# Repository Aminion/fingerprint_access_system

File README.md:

# Fingerprint Access System

## Project Overview

This project implements a complete biometric access control. It handles asynchronous UART communication for fingerprint authentication, ADC measurements for battery diagnostics, and PWM control for physical actuation. The firmware is written entirely in `no_std` Rust, utilizing the Embassy framework for concurrent, event-driven execution without the overhead of a traditional RTOS.

### Core Capabilities
* **Biometric Authentication:** Secure, asynchronous UART communication with a fingerprint module for user enrollment and verification.
* **PWM-Optimized Actuation:** Implementation of a "peak-and-hold" solenoid drive mechanism using Hardware PWM, significantly reducing active power consumption and thermal load.
* **Ratiometric Battery Diagnostics:** A custom ADC measurement strategy utilizing an external TL431 reference to accurately calculate battery capacity, regardless of internal 3.3V rail voltage sag.
* **Zero-State Power Gating:** Physical isolation of analog subsystems (voltage dividers, reference chips) via GPIO-controlled switching, ensuring 0mA draw from these components during system standby.

## Software Stack & Hardware Architecture

### Software
* **Language:** Rust (`no_std`)
* **Framework:** Embassy (Embedded Async)
* **Concurrency Model:** `embassy-executor` for lightweight task scheduling and interrupt management.

### Hardware & Peripherals
* **Microcontroller:** STM32G031K8 (Nucleo-32)
* **Sensor:** GROW R503
* **Power Supply:** 4xAAA NiMH Battery Pack (~4.0V - 6.0V)
* **Peripheral Utilization:**
  * **PWM (Pulse Width Modulation):** Configured to manage the solenoid's current draw, as well as generate user-feedback tones.
  * **ADC (Analog-to-Digital Converter):** Utilizes extended sample timing (`Cycles160_5`) and floating-point calibration math to bypass hardware limitations.
  * **UART (Universal Asynchronous Receiver-Transmitter):** Handles packet-based serial data transfer with the biometric sensor.
  * **GPIO:** Configured for push-pull power switching and standard digital I/O.

## Engineering Challenges Solved

### 1. Solenoid Power Optimization (Peak-and-Hold)
Solenoids require a high initial "pull-in" current to overcome mechanical inertia, but require significantly less current to maintain the unlocked state. Driving a solenoid at 100% duty cycle for the duration of the unlock period wastes battery capacity and generates excess heat.
* **Solution:** The firmware utilizes hardware PWM to drive the actuating transistor. It applies a 100% duty cycle for the initial actuation phase (e.g., 100ms), then instantly drops the duty cycle to a calculated holding percentage (e.g., 30%). This reduces the holding power consumption by up to 70% while keeping the lock disengaged.

### 2. Ratiometric ADC Calibration
On low pin-count STM32 microcontrollers, the analog reference pin (`AREF`) is internally bonded to `VDDA`. Consequently, when the main 3.3V rail sags under load, the ADC reference shifts, causing inaccurate battery readings.
* **Solution:** A TL431 (2.495V) precision external reference was introduced to a standard ADC channel. The firmware samples both the unknown battery voltage and the known TL431 voltage concurrently. By dynamically calculating the deviation of the TL431 reading, the software mathematically reconstructs the true scale of the 3.3V rail, resulting in a highly accurate battery percentage regardless of system load.

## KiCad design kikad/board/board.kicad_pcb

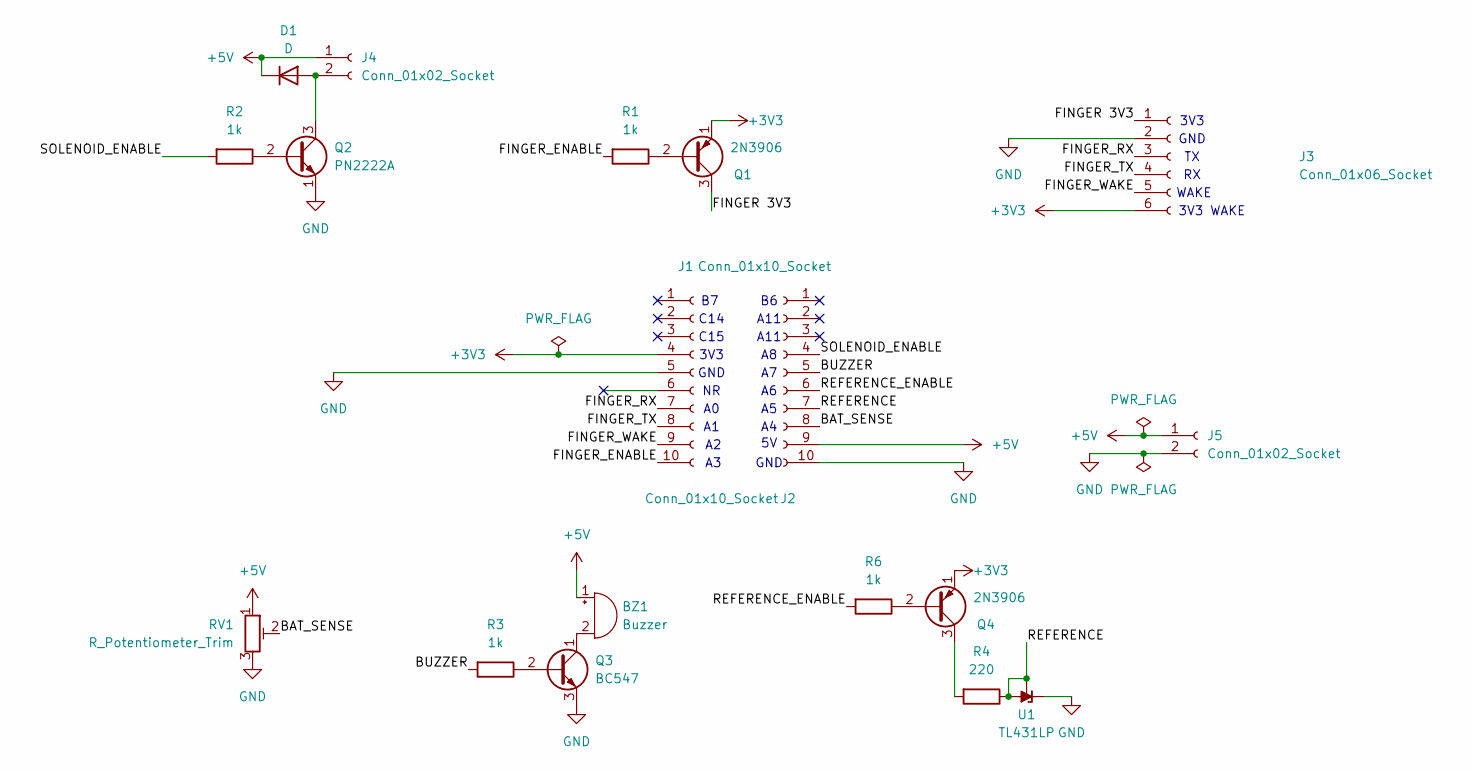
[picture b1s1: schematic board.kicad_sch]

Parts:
BZ1: Buzzer; Buzzer_12x9.5RM7.6
D1: D; D_DO-41_SOD81_P10.16mm_Horizontal
J1: Conn_01x10_Socket; PinSocket_1x10_P2.54mm_Vertical
J2: Conn_01x10_Socket
J3: Conn_01x06_Socket; JST_XH_B6B-XH-A_1x06_P2.50mm_Vertical
J4, J5: Conn_01x02_Socket; JST_XH_B2B-XH-A_1x02_P2.50mm_Vertical
Q1, Q4: 2N3906; TO-92_Inline_Wide
Q2: PN2222A; TO-92_Inline_Wide
Q3: BC547; TO-92_Inline_Wide
R1, R2, R3, R6: 1k; R_Axial_DIN0207_L6.3mm_D2.5mm_P10.16mm_Horizontal
R4: 220; R_Axial_DIN0207_L6.3mm_D2.5mm_P10.16mm_Horizontal
RV1: R_Potentiometer_Trim; Potentiometer_Runtron_RM-065_Vertical
U1: TL431LP; TO-92_Inline_Wide

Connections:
+3V3: J1.4, J3.6, Q1.1 (E), Q4.1 (E)
+5V: BZ1.1 (+), D1.1 (K), J2.9, J4.1, J5.1, RV1.1
/BAT_SENSE: J2.8, RV1.2
/BUZZER: J2.5, R3.2
/FINGER 3V3: J3.1, Q1.3 (C)
/FINGER_ENABLE: J1.10, R1.2
/FINGER_RX: J1.7, J3.3
/FINGER_TX: J1.8, J3.4
/FINGER_WAKE: J1.9, J3.5
/REFERENCE: J2.7, R4.1, U1.1 (REF), U1.2 (A)
/REFERENCE_ENABLE: J2.6, R6.2
/SOLENOID_ENABLE: J2.4, R2.2
GND: J1.5, J2.10, J3.2, J5.2, Q2.1 (E), Q3.3 (E), RV1.3, U1.3 (K)
unnamed: BZ1.2 (-), Q3.1 (C)
unnamed: D1.2 (A), J4.2, Q2.3 (C)
unnamed: Q1.2 (B), R1.1
unnamed: Q2.2 (B), R2.1
unnamed: Q3.2 (B), R3.1
unnamed: Q4.2 (B), R6.1
unnamed: Q4.3 (C), R4.2

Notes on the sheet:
C14
C15
3V3
GND
WAKE
3V3 WAKE
A11

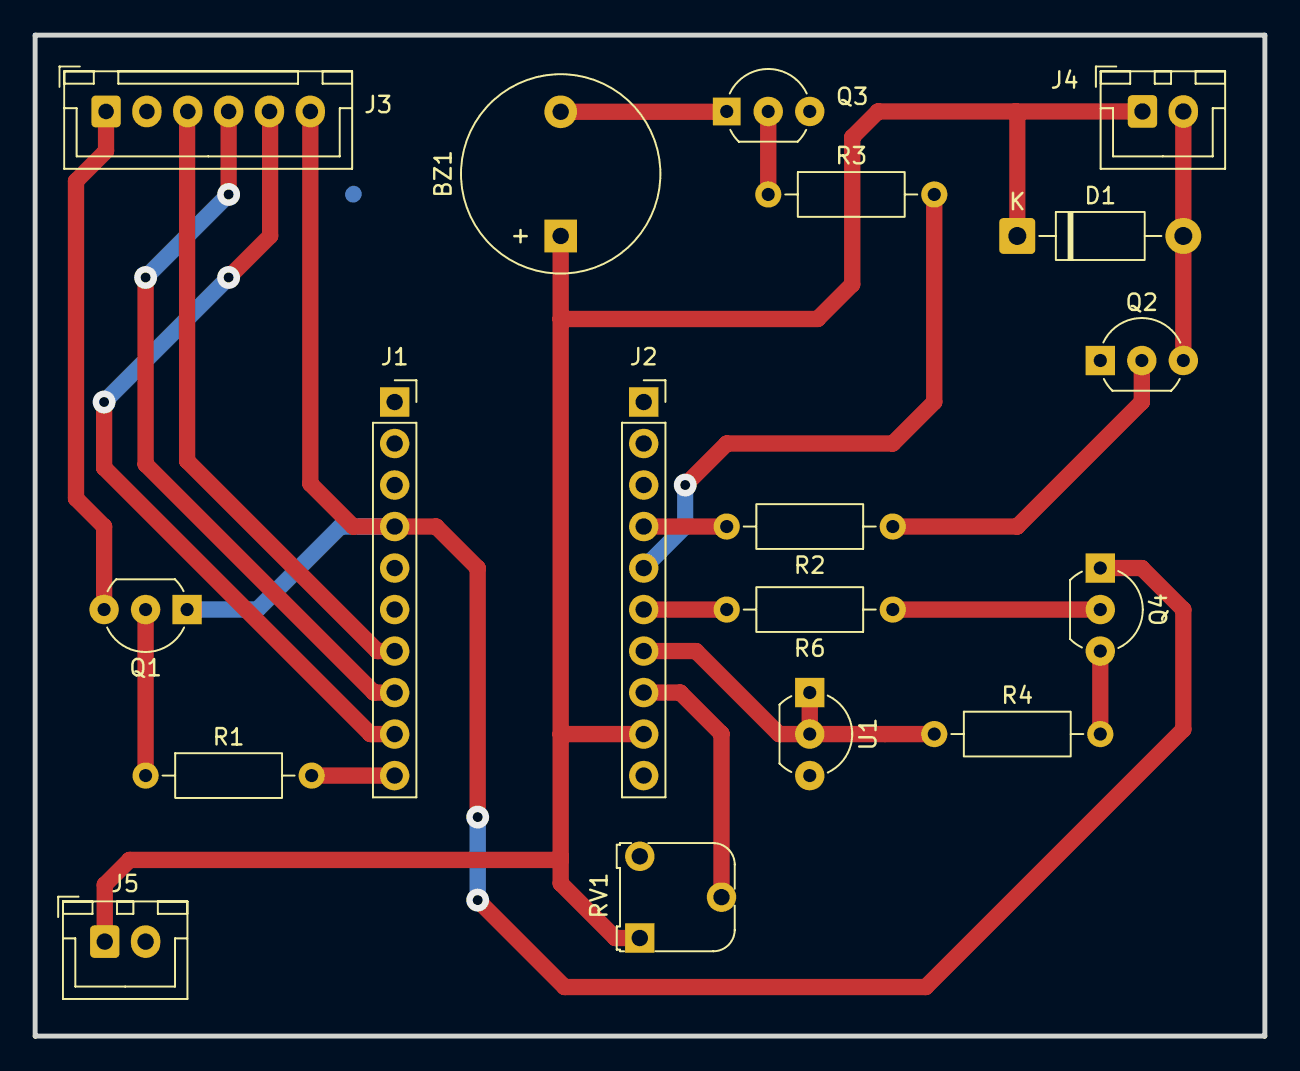
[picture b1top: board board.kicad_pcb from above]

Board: 2 copper layers, 75.2 x 61.2 mm, 18 parts (0 on the bottom side), 20 nets.

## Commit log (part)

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2026-02-24 inital
2026-02-24 size tool
2026-03-02 fingerprint sensore module and his enums
2026-03-02 add ACK fn
2026-03-05 checksum fn
2026-03-05 generic packet cunstruction
2026-03-06 more general packet fn
2026-03-06 try_parse_packet
2026-03-06 gen image
2026-03-08 basic flow
2026-03-10 sensor IRQ handling reworked
2026-03-10 fix IRQ issues
2026-03-10 refactor
2026-03-12 split to files
2026-03-12 led rework
2026-03-12 remove debug code
2026-03-12 fix typos
2026-03-12 removed default fmt
2026-03-13 uart generalization
2026-03-17 battery monitor
2026-03-18 battary efficiency
2026-03-18 battery saver
2026-03-18 beeper task
2026-03-18 Enhance README with project details and capabilities
    Updated project title and added detailed project overview, core capabilities, software stack, hardware architecture, and engineering challenges solved.
2026-03-18 Revise README with project and hardware details
    Updated project description and details about hardware utilization and engineering challenges.
2026-04-10 add kikad scheme
2026-04-13 fix design
2026-04-30 add sensor setup
2026-05-04 await 55 byte from sensor
